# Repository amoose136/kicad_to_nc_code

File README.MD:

## Kicad to NC code
My work has an old pick and place machine that runs on literal DOS era program and silicon. There is currently no way to put a new board design into the machine's memory except by manual training. It does have a floppy disk input however and files and can be read/write to and from the floppy disk. The files are basic enough that simple text manipulation tools should be enough to convert from one format to another.

### Problems
It is unknown how the feeder and other 2 files work and how the data layout works for these files. 

### Approach
The plan is to first create a simple board containing only a 5-10 components in kicad that will be manually be trained using the CNC itself. Once this works, I will save the file to the diskette and copy to a modern computer. From there I attempt to recreate the files using python.

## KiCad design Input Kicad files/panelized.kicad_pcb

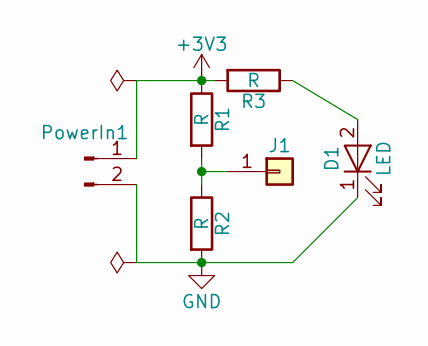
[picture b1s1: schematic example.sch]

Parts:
D1: LED; LED_PLCC_2835
J1: Conn_01x01; Pin_Header_Straight_1x01_Pitch1.00mm
PowerIn1: Conn_01x02_Male; Pin_Header_Straight_1x02_Pitch1.00mm
R1, R2, R3: R; R_1206

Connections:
+3V3: PowerIn1.1, R1.1, R3.2
GND: D1.1 (K), PowerIn1.2, R2.2
unnamed: D1.2 (A), R3.1
unnamed: J1.1, R1.2, R2.1

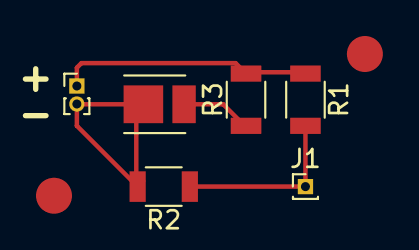
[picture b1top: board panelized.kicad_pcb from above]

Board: 2 copper layers, 8 parts (0 on the bottom side), 4 nets.

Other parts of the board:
FID0, FID1: Fiducial_1mm_Dia_2.54mm_Outer_CopperTop

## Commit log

2017-09-26 🎉 initial commit
2017-09-26 ✨ Add some example nc files
2017-09-26 rename folder
2017-09-26 restore files
2017-10-02 add kicad files
2018-01-05 Add actual working nc data from the smt machine so coding can begin
2018-01-10 add gitignore for pyc files
